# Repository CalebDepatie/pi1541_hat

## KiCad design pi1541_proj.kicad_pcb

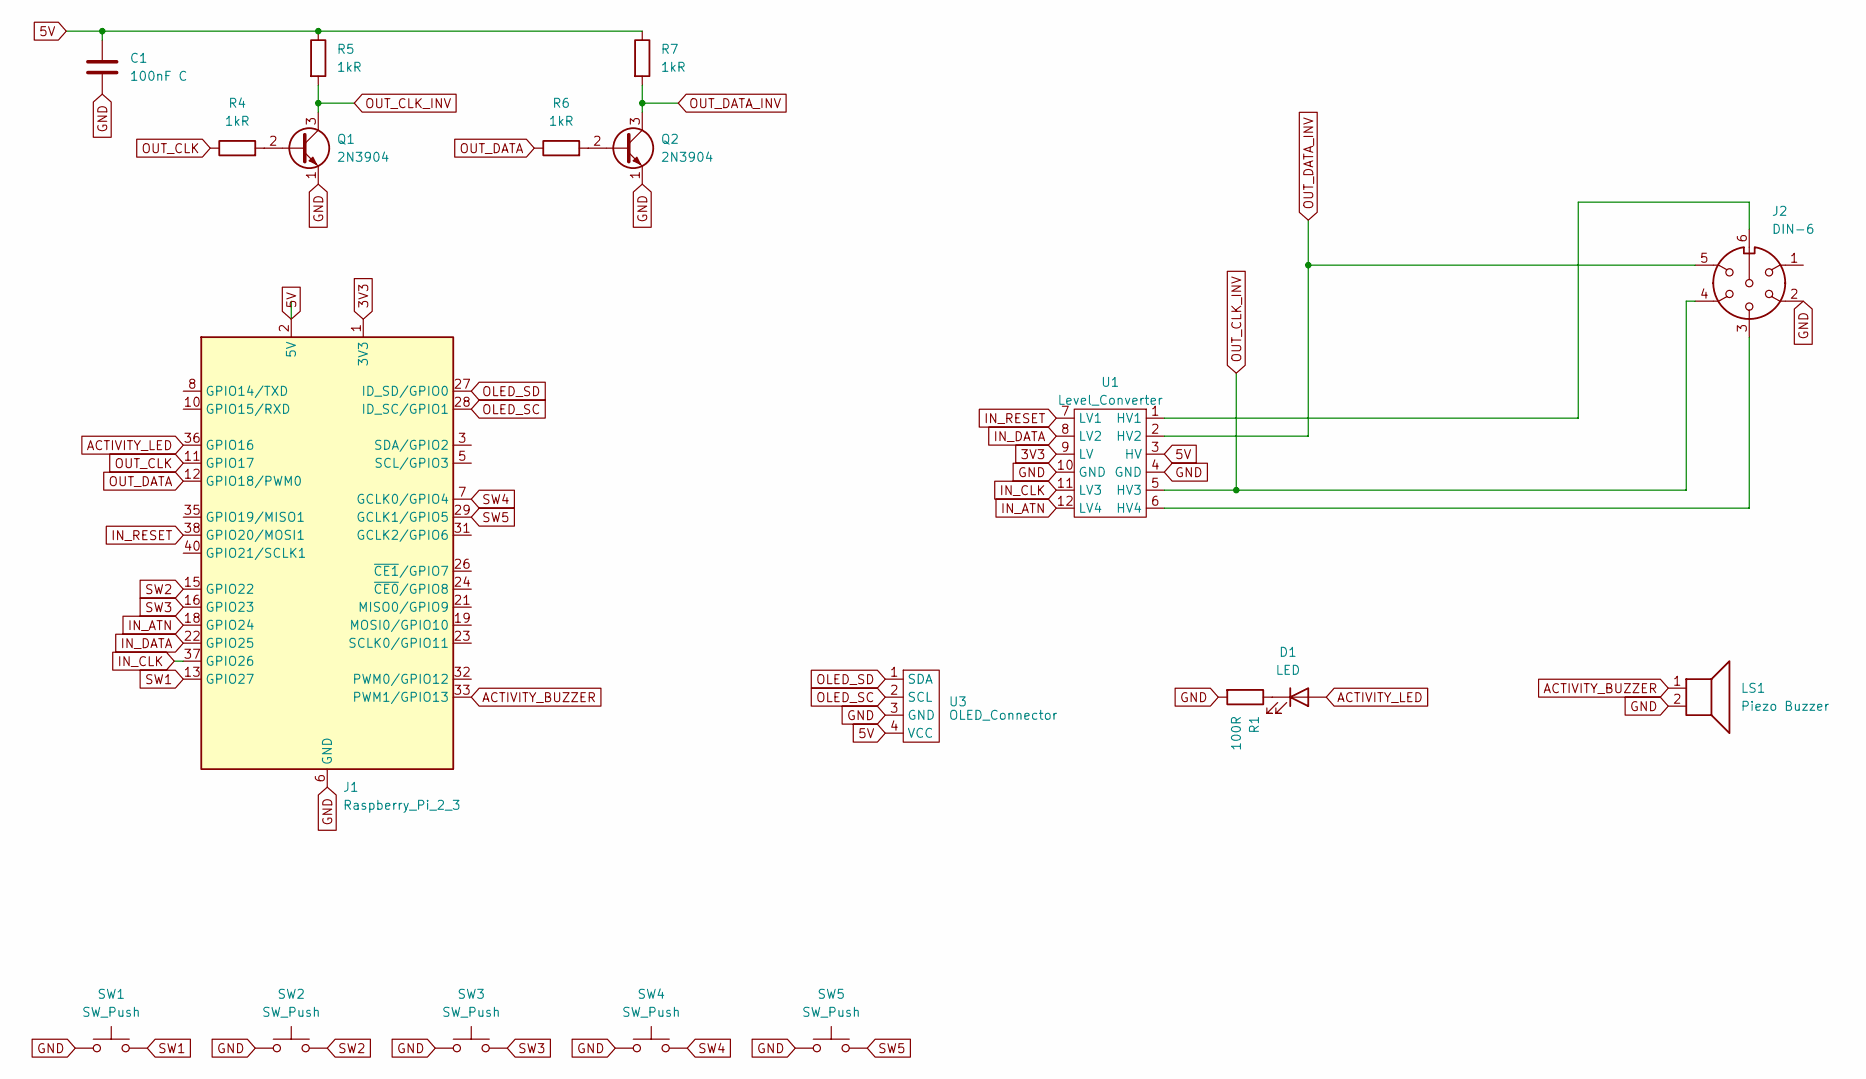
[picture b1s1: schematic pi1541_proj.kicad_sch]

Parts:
C1: 100nF C; C_Rect_L4.0mm_W2.5mm_P2.50mm
D1: LED; LED_D3.0mm
J1: Raspberry_Pi_2_3; PinHeader_2x20_P2.54mm_Vertical
J2: DIN-6; SDF-J_DIN-6
LS1: Piezo Buzzer; PS12_Piezo_Buzzer
Q1, Q2: 2N3904; TO-92_Inline
R1: 100R; R_Box_L8.4mm_W2.5mm_P5.08mm
R4, R5, R6, R7: 1kR; R_Box_L8.4mm_W2.5mm_P5.08mm
SW1, SW2, SW3, SW4, SW5: SW_Push; SW_Cherry_MX_1.00u_PCB
U1: Level_Converter; 12009 Level Converter
U3: OLED_Connector

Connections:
3V3: J1.1 (3V3), J1.17 (3V3), U1.9 (LV)
5V: C1.1, J1.2 (5V), J1.4 (5V), R5.1, R7.1, U1.3 (HV), U3.4 (VCC)
ACTIVITY_BUZZER: J1.33 (PWM1/GPIO13), LS1.1
ACTIVITY_LED: D1.2 (A), J1.36 (GPIO16)
GND: C1.2, J1.6 (GND), J1.9 (GND), J1.14 (GND), J1.20 (GND), J1.25 (GND), J1.30 (GND), J1.34 (GND), J1.39 (GND), J2.2, LS1.2, Q1.1 (E), Q2.1 (E), R1.2, SW1.1, SW2.1, SW3.1, SW4.1, SW5.1, U1.4 (GND), U1.10 (GND), U3.3 (GND)
IN_ATN: J1.18 (GPIO24), U1.12 (LV4)
IN_CLK: J1.37 (GPIO26), U1.11 (LV3)
IN_DATA: J1.22 (GPIO25), U1.8 (LV2)
IN_RESET: J1.38 (GPIO20/MOSI1), U1.7 (LV1)
unnamed: D1.1 (K), R1.1
unnamed: Q1.2 (B), R4.2
unnamed: Q2.2 (B), R6.2
unnamed: J2.6, U1.1 (HV1)
unnamed: J2.3, U1.6 (HV4)
OLED_SC: J1.28 (ID_SC/GPIO1), U3.2 (SCL)
OLED_SD: J1.27 (ID_SD/GPIO0), U3.1 (SDA)
OUT_CLK: J1.11 (GPIO17), R4.1
OUT_CLK_INV: J2.4, Q1.3 (C), R5.2, U1.5 (HV3)
OUT_DATA: J1.12 (GPIO18/PWM0), R6.1
OUT_DATA_INV: J2.5, Q2.3 (C), R7.2, U1.2 (HV2)
SW1: J1.13 (GPIO27), SW1.2
SW2: J1.15 (GPIO22), SW2.2
SW3: J1.16 (GPIO23), SW3.2
SW4: J1.7 (GCLK0/GPIO4), SW4.2
SW5: J1.29 (GCLK1/GPIO5), SW5.2

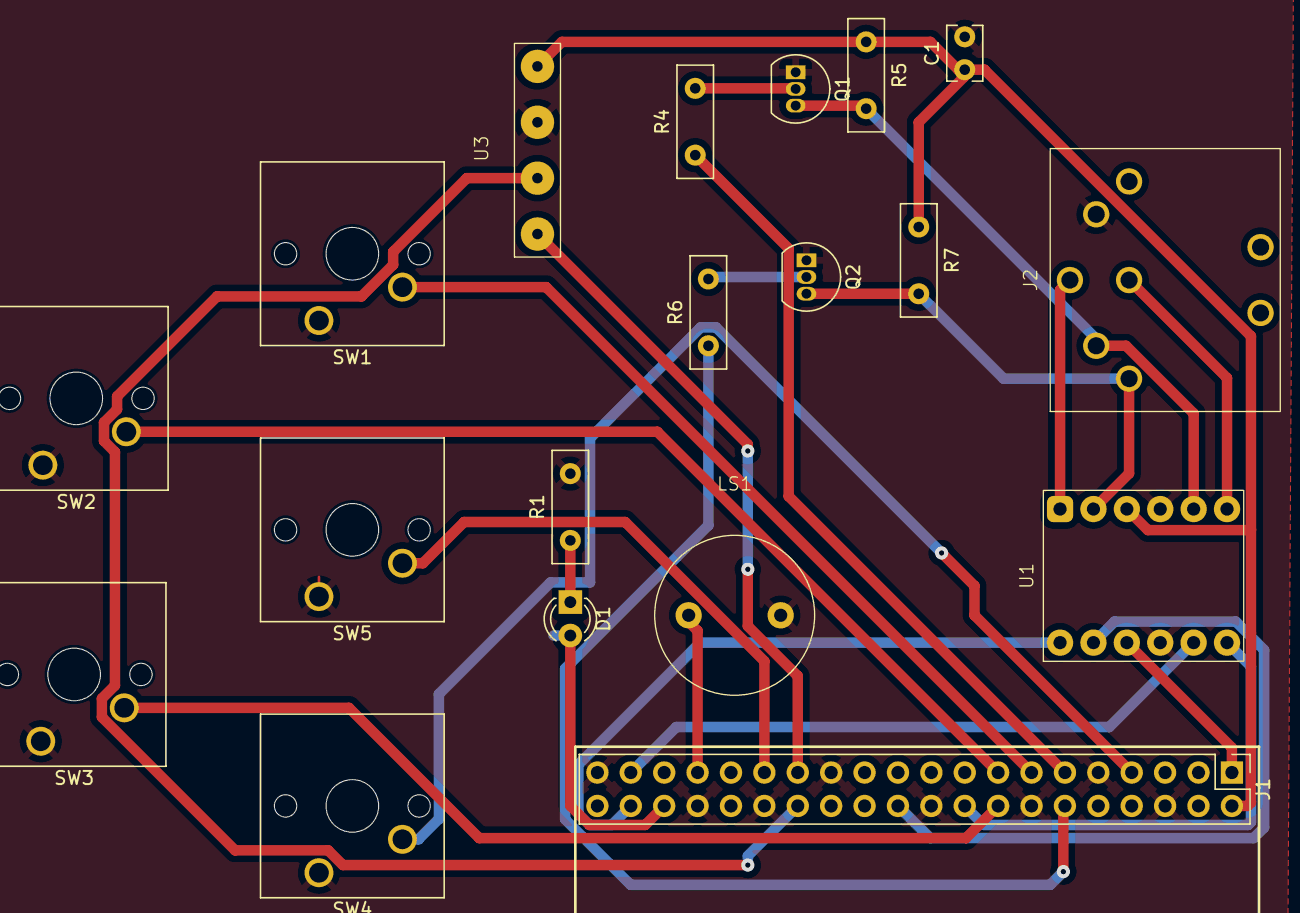
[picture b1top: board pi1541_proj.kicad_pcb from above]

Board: 2 copper layers, 19 parts (0 on the bottom side), 25 nets.

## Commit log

2025-09-16 Initial (bad) schematic
2025-09-22 Switched for a transistor based invertor and improved schematic
